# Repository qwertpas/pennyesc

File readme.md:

# PennyESC, a tiny and cheap brushless motor controller

## Current state of the project:
Works and spins a 1104 motor with closed loop speed and position control! Can daisy chain a few on the same UART bus by using open drain output.

## Nov 14
Finished layout and placed order with JLCPCB! Gerber, BOM, and CPL files in pennyesc/production/

Ended up being about $6/board for raw components, but after setup fees ($16), shipping ($39), and customs ($21) the total was $111 for 5 boards. It should be a lot better when ordering in larger quantities.

## Oct 28
Changed to TI TMAG5273 magnetic angle sensor and TI MCT8316Z power stage for lower price and higher current limit. Price for components should be around $8 per board from JLCPCB. Also thinking of using only 3 mounting holes and allowing for pass through shaft (off-axis magnet sensing). Pass through shaft could be useful for "floating motor" electric muscles.

## Oct 22

* Aiming for $10-15 component cost, around 15 mm diameter
* Assembled by JLCPCB using their in-stock parts
* MP6536 3-phase power stage ($3.38)
    * 5-26 V input
    * 5.5 A current limit
    * PWM input for each half-bridge
    * no current sense
    * 5x5 mm
* MA782 magnetic encoder ($4.11)
    * SPI
    * 2x2 mm
* STM32L011 microcontroller ($1.28)
    * 32 MHz clock
    * 3x3 mm

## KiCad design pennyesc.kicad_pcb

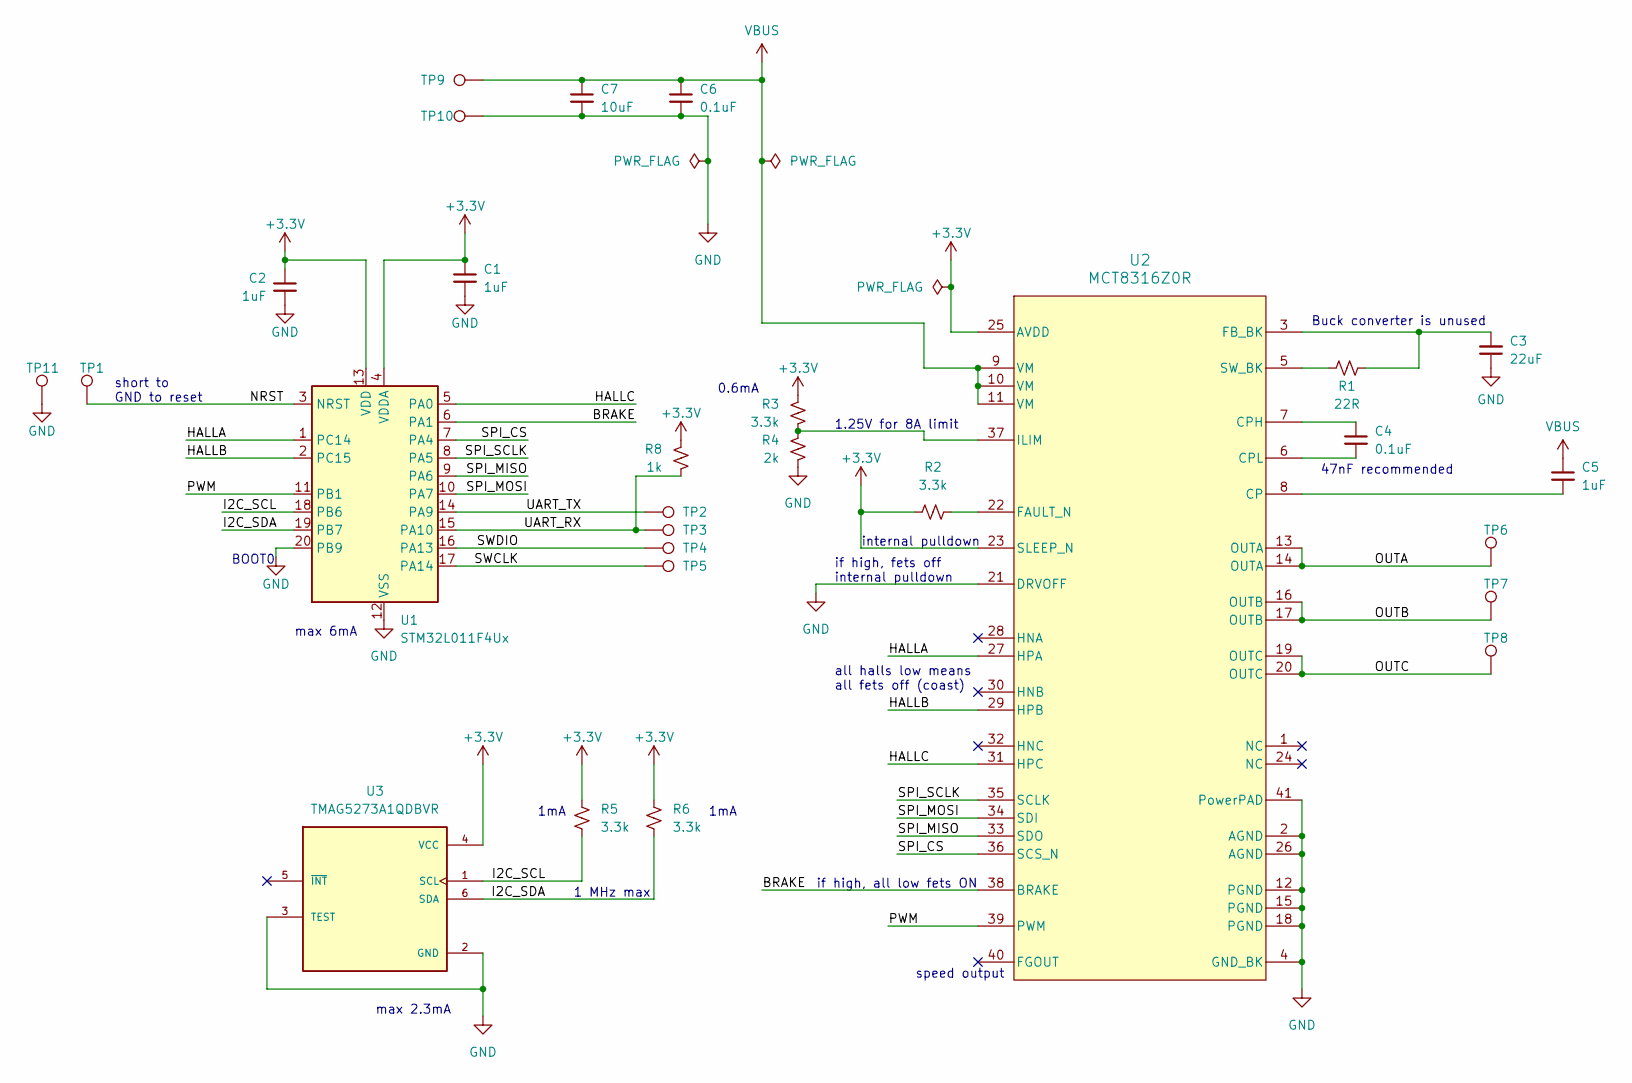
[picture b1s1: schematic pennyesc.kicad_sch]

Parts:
C1, C2: 1uF; C_0402_1005Metric; MPN CL05A105KA5NQNC; JLCPCB C52923
C3: 22uF; C_0603_1608Metric; JLCPCB C59461
C4, C6: 0.1uF; C_0402_1005Metric; JLCPCB C307331
C5: 1uF; C_0402_1005Metric; JLCPCB C52923
C7: 10uF; C_0603_1608Metric; JLCPCB C96446
R1: 22R; R_0402_1005Metric; JLCPCB C25092
R2, R3, R5, R6: 3.3k; R_0402_1005Metric; JLCPCB C25890
R4: 2k; R_0402_1005Metric; JLCPCB C4109
R8: 1k; R_0402_1005Metric; JLCPCB C11702
TP1, TP11: TestPoint; TestPoint_Pad_1mm
TP2, TP3, TP4, TP5: TestPoint; TestPoint_Pad_Rect
TP6, TP7, TP8: TestPoint; SolderHole_1.0x1.6mm
TP9, TP10: TestPoint; Power_Pad_Rect
U1: STM32L011F4Ux; ST_UFQFPN-20_3x3mm_P0.5mm; JLCPCB C329283
U2: MCT8316Z0R; MCT8316Z0RRGFR-IPC_C; JLCPCB C3681397
U3: TMAG5273A1QDBVR; SOT95P280X140-6N; PARTREV B; JLCPCB C3716049

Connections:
+3.3V: C1.1, C2.1, R2.1, R3.1, R5.1, R6.1, R8.1, U1.4 (VDDA), U1.13 (VDD), U2.23 (SLEEP_N), U2.25 (AVDD), U3.4 (VCC)
/BRAKE: U1.6 (PA1), U2.38 (BRAKE)
/HALLA: U1.1 (PC14), U2.27 (HPA)
/HALLB: U1.2 (PC15), U2.29 (HPB)
/HALLC: U1.5 (PA0), U2.31 (HPC)
/I2C_SCL: R5.2, U1.18 (PB6), U3.1 (SCL)
/I2C_SDA: R6.2, U1.19 (PB7), U3.6 (SDA)
/NRST: TP1.1 (1_1), U1.3 (NRST)
/OUTA: TP6.1 (1_1), U2.13 (OUTA), U2.14 (OUTA)
/OUTB: TP7.1 (1_1), U2.16 (OUTB), U2.17 (OUTB)
/OUTC: TP8.1 (1_1), U2.19 (OUTC), U2.20 (OUTC)
/PWM: U1.11 (PB1), U2.39 (PWM)
/SPI_CS: U1.7 (PA4), U2.36 (SCS_N)
/SPI_MISO: U1.9 (PA6), U2.33 (SDO)
/SPI_MOSI: U1.10 (PA7), U2.34 (SDI)
/SPI_SCLK: U1.8 (PA5), U2.35 (SCLK)
/SWCLK: TP5.1 (1_1), U1.17 (PA14)
/SWDIO: TP4.1 (1_1), U1.16 (PA13)
/UART_RX: R8.2, TP3.1 (1_1), U1.15 (PA10)
/UART_TX: TP2.1 (1_1), U1.14 (PA9)
GND: C1.2, C2.2, C3.1, C6.2, C7.2, R4.2, TP10.1 (1_1), TP11.1 (1_1), U1.12 (VSS), U1.20 (PB9), U2.2 (AGND), U2.4 (GND_BK), U2.12 (PGND), U2.15 (PGND), U2.18 (PGND), U2.21 (DRVOFF), U2.26 (AGND), U2.41 (PowerPAD), U3.2 (GND), U3.3 (TEST)
unnamed: C5.2, U2.8 (CP)
unnamed: C4.1, U2.7 (CPH)
unnamed: C4.2, U2.6 (CPL)
unnamed: R2.2, U2.22 (FAULT_N)
unnamed: C3.2, R1.2, U2.3 (FB_BK)
unnamed: R3.2, R4.1, U2.37 (ILIM)
unnamed: R1.1, U2.5 (SW_BK)
VBUS: C5.1, C6.1, C7.1, TP9.1 (1_1), U2.9 (VM), U2.10 (VM), U2.11 (VM)

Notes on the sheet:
internal pulldown
1mA
1 MHz max
Buck converter is unused
short to GND to reset
max 2.3mA
max 6mA
0.6mA
if high, fets off internal pulldown
all halls low means all fets off (coast)
if high, all low fets ON
speed output
1.25V for 8A limit
BOOT0
47nF recommended

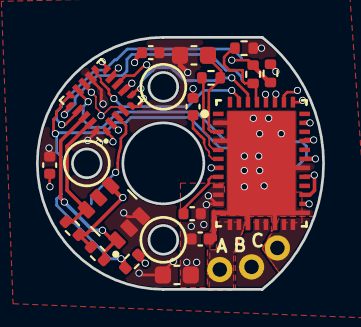
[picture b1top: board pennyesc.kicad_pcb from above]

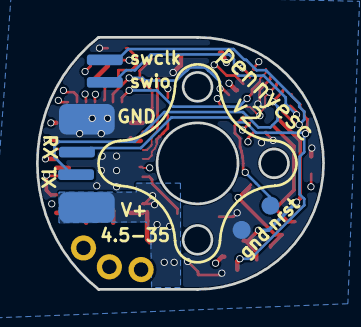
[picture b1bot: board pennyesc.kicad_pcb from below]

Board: 4 copper layers, 15.9 x 14.0 mm, 28 parts (11 on the bottom side), 29 nets.

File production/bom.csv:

Designator,Footprint,Quantity,Value,LCSC Part #
"C1, C2, C5",0402,3,1uF,C52923
C3,0603,1,22uF,C59461
"C4, C6",0402,2,0.1uF,C307331
C7,0603,1,10uF,C96446
R1,0402,1,22R,C25092
"R2, R3, R5, R6, R8",0402,5,3.3k,C25890
R4,0402,1,2k,C4109
U1,ST_UFQFPN-20_3x3mm_P0.5mm,1,STM32L011F4Ux,C329283
U2,MCT8316Z0RRGFR-IPC_C,1,MCT8316Z0RRGFR,C3681249
U3,SOT95P280X140-6N,1,TMAG5273A1QDBVR,C3716049

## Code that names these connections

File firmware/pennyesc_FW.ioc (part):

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Mcu.Name=STM32L011F(3-4)Ux
Mcu.Package=UFQFPN20
Mcu.UserName=STM32L011F4Ux
PA0-CK_IN.Signal=GPIO_Output
PA1.Signal=GPIO_Output
PA10.Mode=Asynchronous
PA10.Signal=USART2_RX
PA13.Mode=Serial_Wire
PA13.Signal=SYS_SWDIO
PA14.Mode=Serial_Wire
PA14.Signal=SYS_SWCLK
PA4.Mode=NSS_Signal_Hard_Output
PA4.Signal=SPI1_NSS
PA5.Mode=Full_Duplex_Master
PA5.Signal=SPI1_SCK
PA6.Mode=Full_Duplex_Master
PA6.Signal=SPI1_MISO
PA7.Mode=Full_Duplex_Master
PA7.Signal=SPI1_MOSI
PA9.Mode=Asynchronous
PA9.Signal=USART2_TX
PB1.Signal=S_TIM2_CH4
PB6.Mode=I2C
PB6.Signal=I2C1_SCL
PB7.Mode=I2C
PB7.Signal=I2C1_SDA
PC14-OSC32_IN.Signal=GPIO_Output
PC15-OSC32_OUT.Signal=GPIO_Output
RCC.HSE_VALUE=8000000
RCC.SYSCLKFreq_VALUE=32000000
RCC.SYSCLKSource=RCC_SYSCLKSOURCE_PLLCLK
board=custom

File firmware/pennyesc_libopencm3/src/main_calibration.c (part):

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/* ============================================================================
 * GPIO Definitions for Motor Control
 * ============================================================================ */
#define HALLA_PORT   GPIOC
#define HALLA_PIN    GPIO14

#define HALLB_PORT   GPIOC
#define HALLB_PIN    GPIO15

#define HALLC_PORT   GPIOA
#define HALLC_PIN    GPIO0

#define BRAKE_PORT   GPIOA
#define BRAKE_PIN    GPIO1

/**
 * Manual Clock Setup for STM32L0
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
static void usart2_setup(void)
{
    // MSP: PA9 (TX), PA10 (RX) -> AF4
    gpio_set_af(GPIOA, GPIO_AF4, GPIO9 | GPIO10);
    gpio_mode_setup(GPIOA, GPIO_MODE_AF, GPIO_PUPD_NONE, GPIO9 | GPIO10);
    gpio_set_output_options(GPIOA, GPIO_OTYPE_OD , GPIO_OSPEED_2MHZ , GPIO9 | GPIO10);
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
static void i2c1_setup(void)
{
    // MSP: PB6 (SCL), PB7 (SDA) -> AF1
    gpio_set_af(GPIOB, GPIO_AF1, GPIO6 | GPIO7);
    gpio_mode_setup(GPIOB, GPIO_MODE_AF, GPIO_PUPD_PULLUP, GPIO6 | GPIO7);
    gpio_set_output_options(GPIOB, GPIO_OTYPE_OD, GPIO_OSPEED_HIGH, GPIO6 | GPIO7);
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
static void tim2_pwm_setup(void)
{
    // MSP: PB1 -> TIM2_CH4 -> AF5
    gpio_set_af(GPIOB, GPIO_AF5, GPIO1);
    gpio_mode_setup(GPIOB, GPIO_MODE_AF, GPIO_PUPD_NONE, GPIO1);

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{
    /* Configure Hall sensor outputs and brake control as push-pull outputs */
    
    /* PC14 - HALLA */
    gpio_mode_setup(HALLA_PORT, GPIO_MODE_OUTPUT, GPIO_PUPD_NONE, HALLA_PIN);
    gpio_set_output_options(HALLA_PORT, GPIO_OTYPE_PP, GPIO_OSPEED_HIGH, HALLA_PIN);
    gpio_clear(HALLA_PORT, HALLA_PIN);  /* Start low */
    
    /* PC15 - HALLB */
    gpio_mode_setup(HALLB_PORT, GPIO_MODE_OUTPUT, GPIO_PUPD_NONE, HALLB_PIN);
    gpio_set_output_options(HALLB_PORT, GPIO_OTYPE_PP, GPIO_OSPEED_HIGH, HALLB_PIN);
    gpio_clear(HALLB_PORT, HALLB_PIN);  /* Start low */
    
    /* PA0 - HALLC */
    gpio_mode_setup(HALLC_PORT, GPIO_MODE_OUTPUT, GPIO_PUPD_NONE, HALLC_PIN);
    gpio_set_output_options(HALLC_PORT, GPIO_OTYPE_PP, GPIO_OSPEED_HIGH, HALLC_PIN);
    gpio_clear(HALLC_PORT, HALLC_PIN);  /* Start low */
    
    /* PA1 - BRAKE */
    gpio_mode_setup(BRAKE_PORT, GPIO_MODE_OUTPUT, GPIO_PUPD_NONE, BRAKE_PIN);
    gpio_set_output_options(BRAKE_PORT, GPIO_OTYPE_PP, GPIO_OSPEED_HIGH, BRAKE_PIN);
    gpio_clear(BRAKE_PORT, BRAKE_PIN);  /* Start with brake off */
}


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         */
        switch (step_count % 6) {
            case 0: // A=1, B=1, C=0
                gpio_set(HALLA_PORT, HALLA_PIN);
                gpio_set(HALLB_PORT, HALLB_PIN);
                gpio_clear(HALLC_PORT, HALLC_PIN);
                break;
            case 1: // A=1, B=0, C=0
                gpio_set(HALLA_PORT, HALLA_PIN);
                gpio_clear(HALLB_PORT, HALLB_PIN);
                gpio_clear(HALLC_PORT, HALLC_PIN);
                break;
            case 2: // A=1, B=0, C=1
                gpio_set(HALLA_PORT, HALLA_PIN);
                gpio_clear(HALLB_PORT, HALLB_PIN);
                gpio_set(HALLC_PORT, HALLC_PIN);
                break;
            case 3: // A=0, B=0, C=1
                gpio_clear(HALLA_PORT, HALLA_PIN);
                gpio_clear(HALLB_PORT, HALLB_PIN);
                gpio_set(HALLC_PORT, HALLC_PIN);
                break;
            case 4: // A=0, B=1, C=1
                gpio_clear(HALLA_PORT, HALLA_PIN);
                gpio_set(HALLB_PORT, HALLB_PIN);
                gpio_set(HALLC_PORT, HALLC_PIN);
                break;
            case 5: // A=0, B=1, C=0
                gpio_clear(HALLA_PORT, HALLA_PIN);
                gpio_set(HALLB_PORT, HALLB_PIN);
                gpio_clear(HALLC_PORT, HALLC_PIN);
                break;
        }
        
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
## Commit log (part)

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2025-10-22 setup and concept
2025-10-26 pin assignment with stm32cube, pick LDO
2025-10-27 switch to cheaper TI parts, passthrough shaft
2025-10-31 chose R and C values, set jlcpcb constraints, started layout
2025-11-14 finish v1 and order from jlcpcb
2025-11-14 pcb mechanical drawing
2025-11-29 omg mag encoder works
2025-11-29 toggle gpio works
2025-11-29 motor spins with basic six step!!
2025-12-24 octant LUT for off axis magnetic encoder, staircase artifacts left
2025-12-24 4900rpm with buggy velocity estimator
2025-12-24 Add multi-turn position tracking and UART command handling for BLDC control, untested
2025-12-25 dma uart rx, untested
2025-12-25 80khz commutation works (0-399 duty, tested up to 200 but mosfet hot), uart pretty consistent
2025-12-25 pennyesc pcb v2 ordered
2026-01-07 generate firmware readme
2026-01-07 change to 40khz commutation, add calibration steps to readme
2026-01-17 rearrange esp32 side wiring
2026-01-18 disable protections for calibration
2026-01-23 update v2 .step and add calibration mcuviewer
2026-01-23 minimal calibration mcuviewer
2026-01-28 test encoder using vertiq, linear plot
2026-01-28 Added encoder.c to measure x,y,z magnetic axis
2026-01-29 added read_z_fast and changed sendCommand in main_encoder.c to use an address
2026-02-12 addressing works
2026-02-20 Added USART Open Drain, verified in hardware with 470 ohm resistor, also added polling and commanding multiple escs at once
2026-02-20 added Lib/esc_address.h
2026-02-21 polling multiple escs, also added procedure for getting UID of MCU
2026-02-21 Added encoder data to polling response packet in main_encoder.c and esp32/main.c, uart currently broken, esc does not send full response
2026-03-02 multiple ESCs are polled by ESP32, requires an external pullup resistor on the ESC TX bus
2026-03-02 collected calibration data
2026-03-02 added calibration data
2026-03-06 recalibrate uid 59
2026-03-06 flash uid 59 calibration
2026-03-06 dedicated motor test
2026-04-13 encoder and magpoll gui
2026-04-13 ignore pcb history and backups
2026-04-13 update gitignore
2026-04-20 automated calibration gui, uart bootloader, and arduino lib (still buggy)
2026-04-21 dynamic calibration barely works, advance angle and angle estimation messed up
2026-04-26 main stepper finally works because spi fixed
2026-04-26 spins well, but startup steps remain in main
2026-04-26 remove startup steps
2026-04-26 speed up ISR to 10khz
2026-04-26 mct fault recovery and status
2026-04-27 fast tmag 1x XY during run mode
2026-04-27 simple angle estimator delay 250us
2026-04-27 tune observer lead metrics
2026-04-27 add selectable observer filters
2026-04-27 test new observers, velocity estimation noisy so kcv not starting baseline
2026-04-27 stop tracking .history and update gitignore
2026-04-27 probably fixed tmag XY only mode
2026-04-28 filter velocity, attempt observer tune
2026-04-28 working scheduled 10hz isr
2026-04-28 checkpoint tim21 scheduler tmag reads
2026-04-28 restore lead compensation in scheduler fallback
2026-04-28 remove hybrid commutation fallback
2026-04-28 use fresh commutation timestamp
2026-04-30 spins up to 16krpm but speed saturates. attempting better angle estimation
2026-05-04 Untested changes to commutation, angle units, and calibration - add CC2 scheduled commutation and timestamp fixes for higher speed - switch status/position protocol fields from crad to turn32 units -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
2026-05-04 pwm tester
2026-05-05 commutaiton works agin
2026-05-05 postiion code mostly works
2026-05-05 position control and new protocol
2026-05-07 works again?
2026-05-07 commutation works again on esc4
2026-05-07 calibration now persists advance degree
2026-05-07 calibration fixed
2026-05-07 example bridge firmware
2026-05-07 cleaned up user side penny lib a little
2026-05-07 921600 baud
2026-05-07 faster tmag read and slightly less noisy velocity
2026-05-07 speed up gui and reduce tiemouts
2026-05-11 tune velocity observer
2026-05-12 update firmware readme
2026-05-12 power testing
2026-05-12 remove test session from git
2026-05-12 add capacitor recommendation to readme
2026-05-12 low level protocol readme
2026-05-12 remove local settings and plan
2026-05-12 Remove dynamic metrics artifacts
2026-05-12 angle read delay compensation 180us
2026-05-12 remove vscode settings
2026-05-12 faultn pullup should be 1k
2026-05-12 cleanup and refactor main
2026-05-12 200ms capture buffer, arduino api and doc
2026-05-12 untested advance sweep after observer delay
2026-05-14 fixed sweep bug that was not using right lead time
2026-05-18 speed up address scan
2026-05-18 tristate tx instead of open drain, no need for pullup anymore
2026-05-19 checkpoint firmware polling diagnostics
2026-05-19 add live posvel fast path
2026-05-20 revert unsafe uart fast path
2026-05-20 Add ESP fast poll rate test
2026-05-20 faster mct spi
2026-05-20 split off arduino lib debug
2026-05-25 3x position sweep example
2026-06-04 observer tune
